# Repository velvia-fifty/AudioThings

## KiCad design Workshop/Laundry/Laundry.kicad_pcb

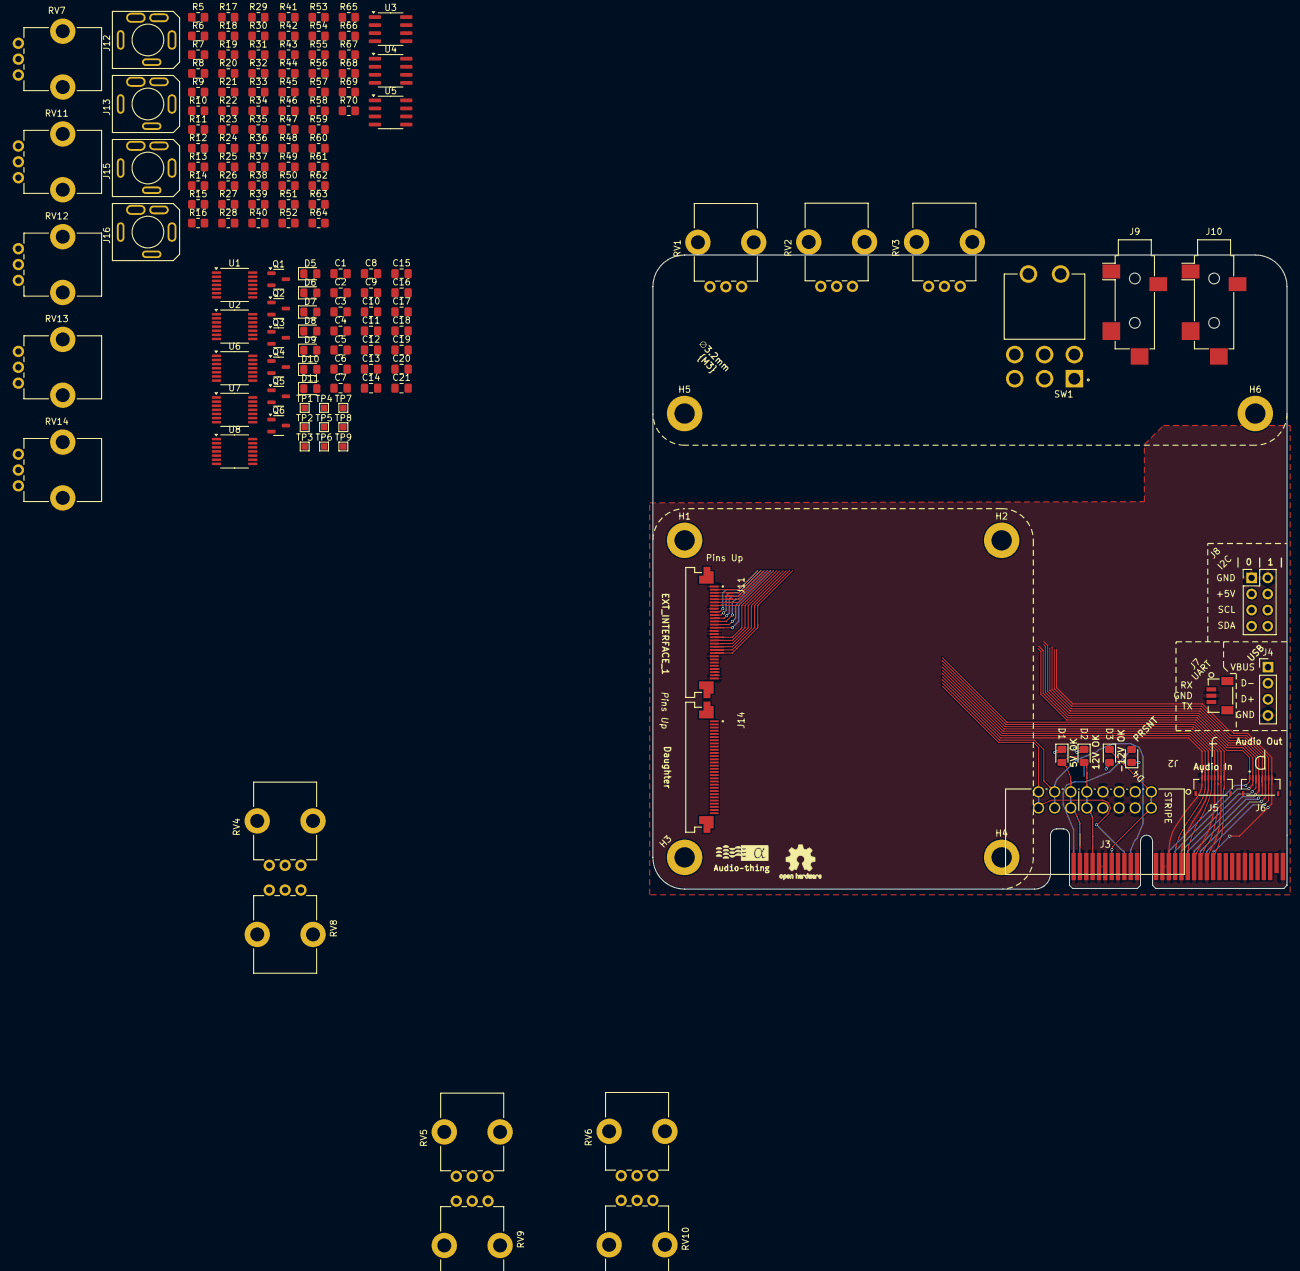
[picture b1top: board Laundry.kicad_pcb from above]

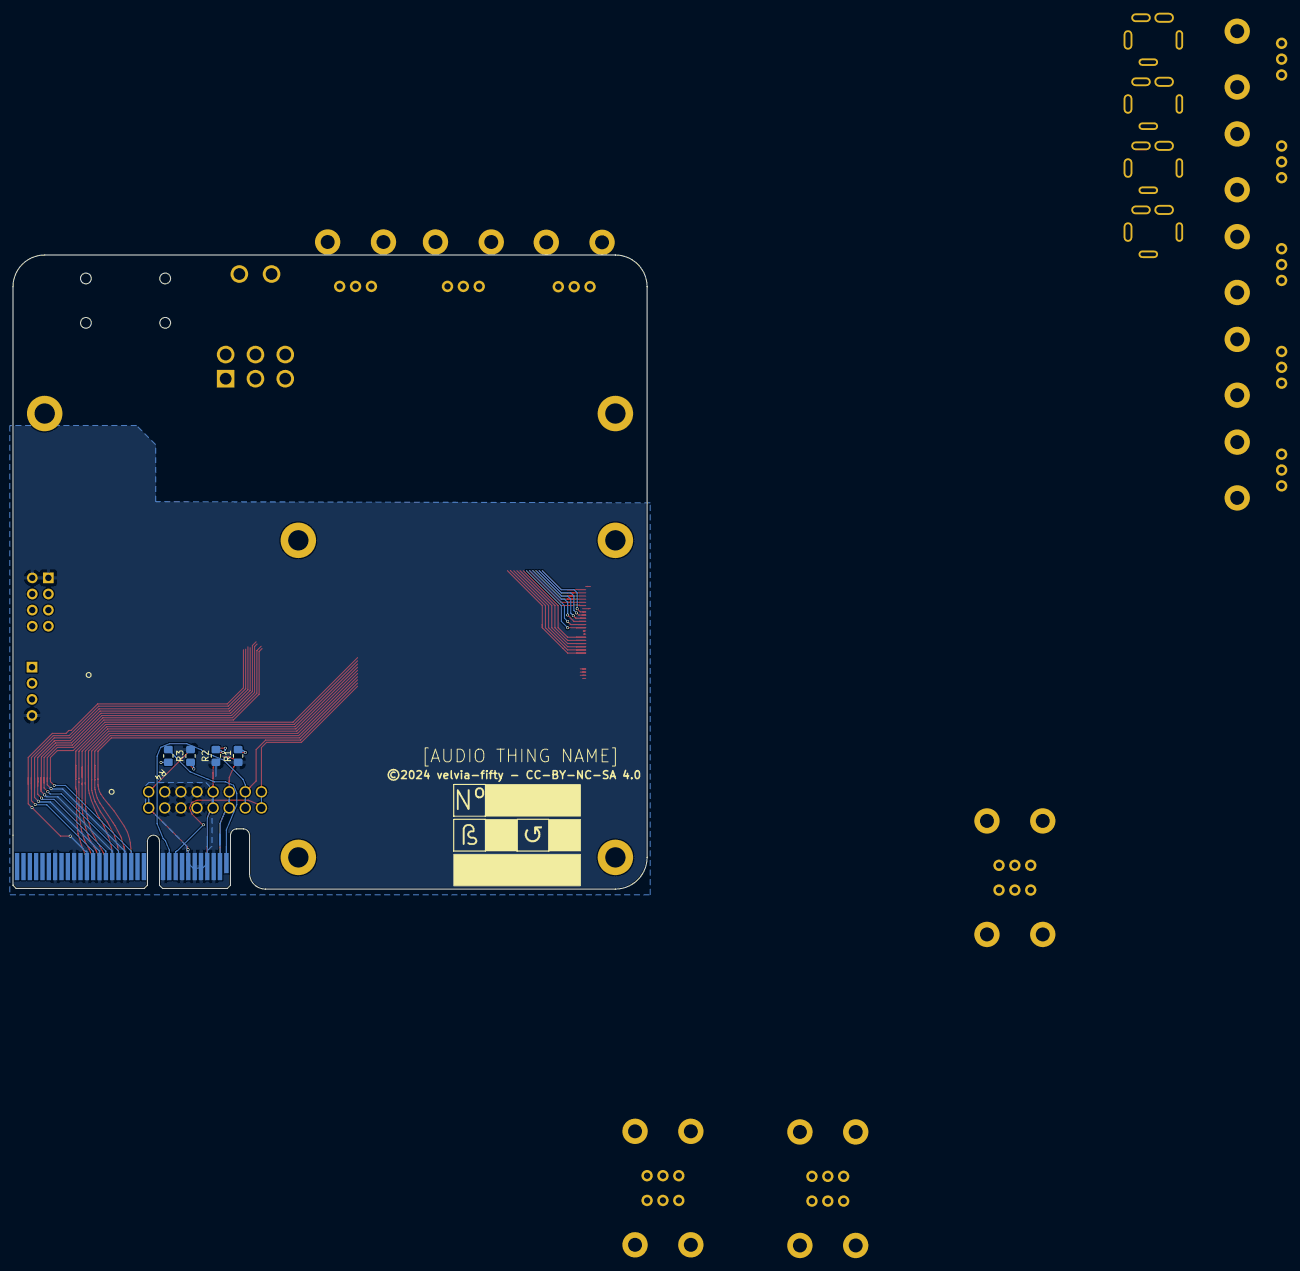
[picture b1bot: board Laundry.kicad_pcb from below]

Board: 2 copper layers, 100.0 x 100.0 mm, 161 parts (4 on the bottom side), 108 nets.

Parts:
C1: 10uf; C_0805_2012Metric_Pad1.18x1.45mm_HandSolder
C2: 1uf; C_0805_2012Metric_Pad1.18x1.45mm_HandSolder
C3: 100uf; C_0805_2012Metric_Pad1.18x1.45mm_HandSolder
C4, C5, C6: 100nf; C_0805_2012Metric_Pad1.18x1.45mm_HandSolder
C7, C8: 4.7nF; C_0805_2012Metric_Pad1.18x1.45mm_HandSolder
C9: 220nF; C_0805_2012Metric_Pad1.18x1.45mm_HandSolder
C10, C11: 100nF; C_0805_2012Metric_Pad1.18x1.45mm_HandSolder
C12: 10uF; C_0805_2012Metric_Pad1.18x1.45mm_HandSolder
C13: 68nF; C_0805_2012Metric_Pad1.18x1.45mm_HandSolder
C14, C21: 5.6nF; C_0805_2012Metric_Pad1.18x1.45mm_HandSolder
C15, C20: 2.2nF; C_0805_2012Metric_Pad1.18x1.45mm_HandSolder
C16, C18: 1uF; C_0805_2012Metric_Pad1.18x1.45mm_HandSolder
C17: 680p; C_0805_2012Metric_Pad1.18x1.45mm_HandSolder
C19: 680pF; C_0805_2012Metric_Pad1.18x1.45mm_HandSolder
D1: 5V OK; LED_0805_2012Metric_Pad1.15x1.40mm_HandSolder
D2: 12V OK; LED_0805_2012Metric_Pad1.15x1.40mm_HandSolder
D3: -12V OK; LED_0805_2012Metric_Pad1.15x1.40mm_HandSolder
D4: PRSNT; LED_0805_2012Metric_Pad1.15x1.40mm_HandSolder
D5, D6, D7: OSC; LED_0805_2012Metric_Pad1.15x1.40mm_HandSolder
D8, D9, D10: 1N4001; D_0805_2012Metric_Pad1.15x1.40mm_HandSolder
D11: LFO; LED_0805_2012Metric_Pad1.15x1.40mm_HandSolder
H1, H2, H3, H4, H5, H6: M3; MountingHole_3.2mm_M3_DIN965_Pad
J2: OPT EURO; EURORACK Right Angle
J3: BUS_PCIexpress_x4
J4: USB; PinHeader_1x04_P2.54mm_Vertical
J5: Audio In; AMPHENOL_F33B-1A7Q1-E8C08
J6: Audio Out; AMPHENOL_F33B-1A7Q1-E8C08
J7: UART; CONN_BM03B-SRSS-TBLFSN_JST
J8: I2C; PinHeader_2x04_P2.54mm_Vertical
J9, J10: Stereo Jack - SMD HZ; SMD_STEREO_CUI_SJ-3524-SMT_Horizontal
J11: EXT_INTERFACE_1; AMPHENOL_SFV30R-4STE1HLF - FFC - 30 RA
J12: TRI MIX OUT; SJ3-3505
J13: FOLD IN; SJ3-3505
J14: Daughter; AMPHENOL_SFV30R-4STE1HLF - FFC - 30 RA
J15: SYNC OUT; SJ3-3505
J16: SYNC IN; SJ3-3505
Q1, Q2: BC558; SOT-23-3
Q3, Q4, Q5, Q6: BC548; SOT-23-3
R1, R4: 150; R_0805_2012Metric_Pad1.20x1.40mm_HandSolder
R2, R3: 500; R_0805_2012Metric_Pad1.20x1.40mm_HandSolder
R5, R6, R7: 2k; R_0805_2012Metric_Pad1.20x1.40mm_HandSolder
R8, R9, R10, R14, R16, R18, R20, R22, R24, R38, R46, R48, R51, R59, R62: 1k; R_0805_2012Metric_Pad1.20x1.40mm_HandSolder
R11, R12, R13, R37, R40, R49, R52, R54, R58, R60, R61, R63, R64, R68: 100k; R_0805_2012Metric_Pad1.20x1.40mm_HandSolder
R15, R17, R19, R33, R35, R39, R41, R55: 10k; R_0805_2012Metric_Pad1.20x1.40mm_HandSolder
R21, R23, R25, R47: 1M; R_0805_2012Metric_Pad1.20x1.40mm_HandSolder
R26: 1.5k; R_0805_2012Metric_Pad1.20x1.40mm_HandSolder
R27, R43: 220k; R_0805_2012Metric_Pad1.20x1.40mm_HandSolder
R28: 100R; R_0805_2012Metric_Pad1.20x1.40mm_HandSolder
R29, R30, R31, R42, R44, R53: 20k; R_0805_2012Metric_Pad1.20x1.40mm_HandSolder
R32: 200k; R_0805_2012Metric_Pad1.20x1.40mm_HandSolder
R34: 51k; R_0805_2012Metric_Pad1.20x1.40mm_HandSolder
R36, R45, R57, R69: 680R; R_0805_2012Metric_Pad1.20x1.40mm_HandSolder
R50, R67: 470k; R_0805_2012Metric_Pad1.20x1.40mm_HandSolder
R56: 33k; R_0805_2012Metric_Pad1.20x1.40mm_HandSolder
R65: 4k7; R_0805_2012Metric_Pad1.20x1.40mm_HandSolder
R66: 47k; R_0805_2012Metric_Pad1.20x1.40mm_HandSolder
R70: 22k; R_0805_2012Metric_Pad1.20x1.40mm_HandSolder
RV1, RV2, RV3: PTV09 Pot HZ; Potentiometer_Bourns_PTV09A-1_Single_Vertical
RV4, RV5: 250k; Potentiometer_Bourns_PTV09A-1_Single_Vertical
RV6, RV8, RV9, RV10: 100k; Potentiometer_Bourns_PTV09A-1_Single_Vertical
RV7, RV11, RV13, RV14: 10k; Potentiometer_Bourns_PTV09A-1_Single_Vertical
RV12: 1M; Potentiometer_Bourns_PTV09A-1_Single_Vertical
SW1: Micro Toggle; DPDT Micro SW_1825138-7
TP1: SYNC1; TestPoint_Pad_1.0x1.0mm
TP2: SYNC2; TestPoint_Pad_1.0x1.0mm
TP3: SYNC3; TestPoint_Pad_1.0x1.0mm
TP4: SYNC4; TestPoint_Pad_1.0x1.0mm
TP5: TRI_A; TestPoint_Pad_1.0x1.0mm
TP6: WHT1; TestPoint_Pad_1.0x1.0mm
TP7: BLUE; TestPoint_Pad_1.0x1.0mm
TP8: WHT2; TestPoint_Pad_1.0x1.0mm
TP9: PINK; TestPoint_Pad_1.0x1.0mm
U1: 40106; TSSOP-14_4.4x5mm_P0.65mm
U2, U6, U7, U8: TL074; TSSOP-14_4.4x5mm_P0.65mm
U3, U4, U5: TL072; SOIC-8_3.9x4.9mm_P1.27mm

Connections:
+5V: D1.2 (A), J2.11, J2.12, J3.A2 (+5V), J3.B2 (+5V), J8.3, J8.4
+12V: D2.2 (A), J2.9, J2.10, J3.A4 (+12V), J3.B4 (+12V), R29.1, R30.1, R37.1, R49.1, R60.1
-12V: D3.1 (K), J2.1, J2.2, J3.A7 (-12V), J3.B7 (-12V), R42.2, R44.2
/Bus/CON_CV: J2.13, J2.14, J3.A10 (EURO_CV)
/Bus/CON_GATE: J2.15, J2.16, J3.A9 (EURO_GATE)
/Bus/I2C0_SCL: J3.B23 (I2C0_SCL), J8.5
/Bus/I2C0_SDA: J3.A24 (I2C0_SDA), J8.7
/Bus/I2C1_SCL: J3.A27 (I2C1_SCL), J8.6
/Bus/I2C1_SDA: J3.B27 (I2C1_SDA), J8.8
/Bus/USB_D+: J3.B12 (USB_D+), J4.3
/OSC/BLUE: R51.2, TP7.1
/OSC/FMV_IN: C7.1, R26.1
/OSC/FOLD_0_IN: J13.T, R34.2, TP5.1
/OSC/PINK: R62.2, TP9.1
/OSC/SQ_LOW_0: C4.2, R21.1
/OSC/SQ_MID_0: C5.2, R23.1
/OSC/SQ_TRB_0: C6.2, R25.1
/OSC/SYNC_IN_0: D8.2 (A), J16.T, TP1.1
/OSC/TRI_LOW_0: R14.2, R20.1, RV8.3
/OSC/TRI_MID_0: R16.2, R22.1, RV9.3
/OSC/TRI_TRB_0: R18.2, R24.1, RV10.3
/OSC/WHT_1: R48.1, TP6.1
/OSC/WHT_2: R59.1, TP8.1
GND: C1.1, C2.1, C3.1, C12.2, C13.1, D11.1 (K), J2.3, J2.4, J2.5, J2.6, J2.7, J2.8, J3.A3 (GND), J3.A5 (GND), J3.A6 (GND), J3.A8 (GND), J3.A11 (GND), J3.A15 (GND), J3.A17 (GND), J3.A19 (GND), J3.A21 (GND), J3.A23 (GND), J3.A26 (GND), J3.B1 (GND), J3.B3 (GND), J3.B5 (GND), J3.B6 (GND), J3.B8 (GND), J3.B11 (GND), J3.B13 (GND), J3.B14 (GND), J3.B16 (GND), J3.B18 (GND), J3.B20 (GND), J3.B26 (GND), J3.B32 (GND), J4.4, J5.1, J5.3, J5.5, J5.7, J6.2, J6.4, J6.6, J6.8, J7.2, J8.1, J8.2, J11.1, J11.8, J11.15, J11.16, J11.23, J11.30, J12.S, J13.S, J15.S, J16.S, Q5.2 (B), Q6.2 (B), R1.1, R2.1, R3.2, R5.1, R6.1, R7.1, R15.2, R17.2, R19.2, R20.2, R21.2, R22.2, R23.2, R24.2, R25.2, R40.2, R45.2, R46.2, R52.2, R53.2, R57.2, R58.2, R63.2, R65.2, R66.2, R67.2, R69.2, R70.2, RV8.1, RV9.1, RV10.1, RV11.3, RV14.3, U4.3 (+), U5.3 (+)
unnamed: C1.2, R8.1, R14.1, RV4.2, RV4.3, U1.3
unnamed: C2.2, R9.1, R16.1, RV5.2, RV5.3, U1.5
unnamed: C3.2, R10.1, R18.1, RV6.2, RV6.3, U1.11
unnamed: C7.2, C8.2, RV7.1
unnamed: C8.1, R28.1
unnamed: C9.2, RV11.2
unnamed: C10.2, R39.1, R43.2, U6.1
unnamed: C11.1, R45.1, RV14.2
unnamed: C9.1, C11.2, R26.2, R36.1
unnamed: C13.2, R36.2, RV7.3, RV14.1
unnamed: C14.1, C15.1, C17.1, R48.2, R54.2, U8.1
unnamed: C14.2, R47.1
unnamed: C15.2, R50.1
unnamed: C17.2, R55.1
unnamed: C19.1, R65.1
unnamed: C20.1, R66.1
unnamed: C21.1, R67.1
unnamed: D1.1 (K), R1.2
unnamed: D2.1 (K), R2.2
unnamed: D3.2 (A), R3.1
unnamed: D4.2 (A), J3.B31 (PRSNT_B)
unnamed: D4.1 (K), R4.2
unnamed: D5.2 (A), D9.2 (A), R11.1, RV4.1, TP2.1, U1.4
unnamed: D5.1 (K), R5.2
unnamed: D6.1 (K), R6.2
unnamed: D7.2 (A), R13.1, RV6.1, TP4.1, U1.10
unnamed: D7.1 (K), R7.2
unnamed: D8.1 (K), R8.2
unnamed: D9.1 (K), R9.2
unnamed: D6.2 (A), D10.2 (A), R12.1, RV5.1, TP3.1, U1.6
unnamed: D10.1 (K), R10.2
unnamed: D11.2 (A), R41.1
unnamed: J3.B15 (Audio_In_A), J5.2
unnamed: J3.B17 (Audio_In_B), J5.4
unnamed: J3.B19 (Audio_In_C), J5.6
unnamed: J3.B21 (Audio_In_D), J5.8
unnamed: J3.A14 (Audio_Out_A), J6.1
unnamed: J3.A16 (Audio_Out_B), J6.3
unnamed: J3.A18 (Audio_Out_C), J6.5
unnamed: J3.A20 (Audio_Out_D), J6.7
unnamed: J3.A1 (PRSNT_A), R4.1
unnamed: J3.B22 (UART_RX), J7.1
unnamed: J3.A22 (UART_TX), J7.3
unnamed: J3.A12 (USB_5V), J4.1
unnamed: J3.A13 (USB_D-), J4.2
unnamed: J12.T, J13.TN, RV8.2, RV9.2, RV10.2
unnamed: Q1.2 (B), Q3.2 (B), U3.1, U3.2 (-)
unnamed: Q1.1 (C), Q3.1 (C), R33.2
unnamed: Q1.3 (E), R29.2
unnamed: Q2.2 (B), Q4.2 (B), R31.2, U4.1
unnamed: Q2.1 (C), Q4.1 (C), R35.2
unnamed: Q2.3 (E), R30.2
unnamed: Q3.3 (E), R42.1
unnamed: Q4.3 (E), R44.1
unnamed: C16.1, Q5.3 (E), R49.2
unnamed: C18.1, Q6.3 (E), R60.2
unnamed: R28.2, RV11.1
unnamed: R32.2, R38.2, U5.1
unnamed: R39.2, RV12.2, RV12.3
unnamed: R46.1, RV13.2, RV13.3
unnamed: R51.1, R56.2, U8.8
unnamed: R59.2, R61.1, R64.2, U8.7
unnamed: R62.1, R68.2, U8.14
unnamed: R11.2, R15.1, U2.3 (+)
unnamed: C4.1, U2.1, U2.2 (-)
unnamed: R12.2, R17.1, U2.5 (+)
unnamed: C5.1, U2.6 (-), U2.7
unnamed: R13.2, R19.1, U2.12 (+)
unnamed: C6.1, U2.13 (-), U2.14
unnamed: R34.1, RV13.1, U3.3 (+)
unnamed: R31.1, R33.1, U4.2 (-)
unnamed: R32.1, R35.1, U5.2 (-)
unnamed: C10.1, R27.1, U6.3 (+)
unnamed: R37.2, R40.1, R43.1, U6.2 (-)
unnamed: C12.1, R27.2, RV12.1, U7.3 (+)
unnamed: J15.T, J16.TN, R41.2, U7.1, U7.2 (-)
unnamed: C16.2, R52.1, U8.3 (+)
unnamed: R54.1, R57.1, U8.2 (-)
unnamed: C18.2, R63.1, U8.5 (+)
unnamed: R64.1, R69.1, U8.6 (-)
unnamed: R47.2, R50.2, R53.1, R55.2, U8.10 (+)
unnamed: R56.1, R58.1, U8.9 (-)
unnamed: C19.2, C20.2, C21.2, R61.2, U8.12 (+)
unnamed: R68.1, R70.1, U8.13 (-)

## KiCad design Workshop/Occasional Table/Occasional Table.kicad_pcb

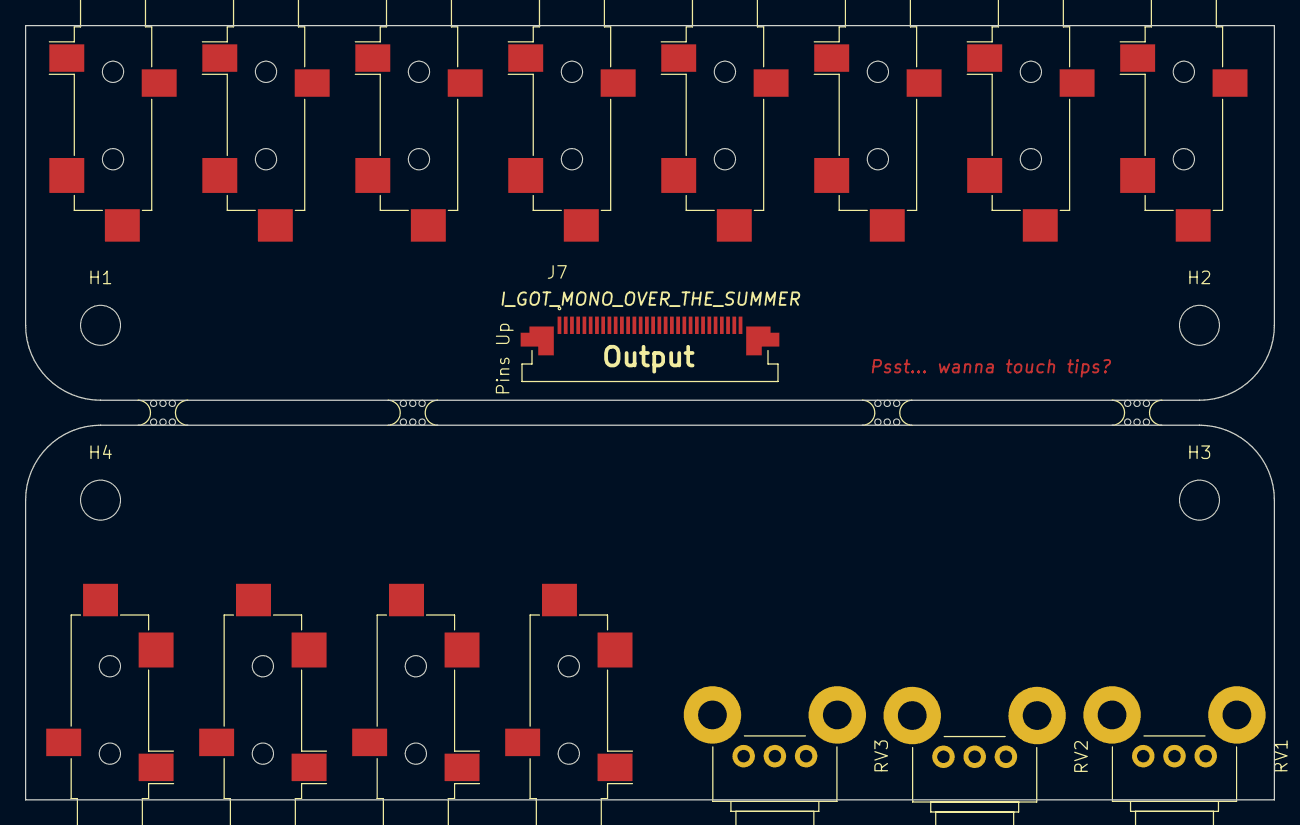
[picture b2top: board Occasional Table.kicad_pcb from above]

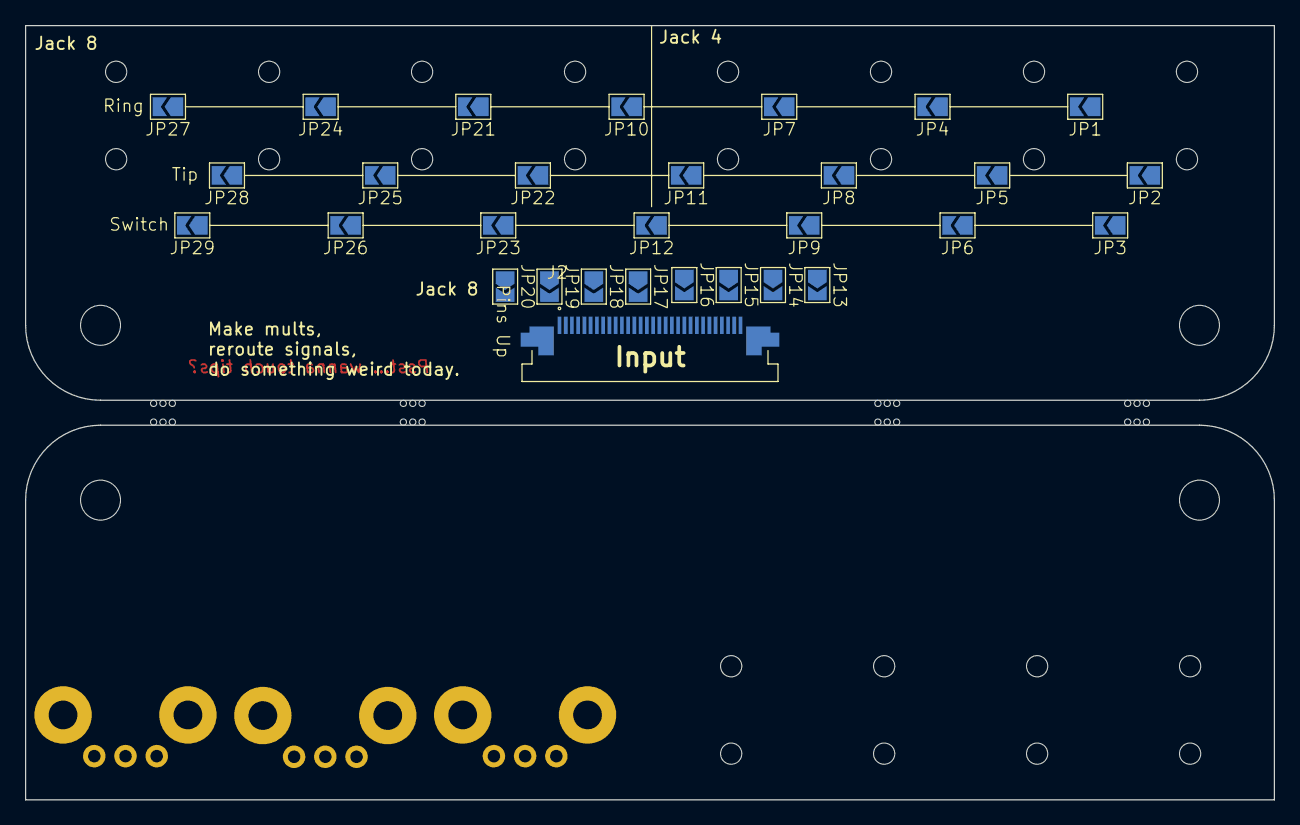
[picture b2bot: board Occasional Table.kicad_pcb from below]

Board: 2 copper layers, 100.0 x 62.0 mm, 54 parts (30 on the bottom side), 33 nets, no tracks yet.

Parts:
H1, H2, H3, H4: Spacer M3; MountingHole_3.2mm_M3_DIN965
J1: Jack 1; Jack_3.5mm_CUI_SJ-3524-SMT_Horizontal
J2: EXT_INTERFACE_1; AMPHENOL_SFV30R-4STE1HLF - FFC - 30 RA
J4: Jack 2; Jack_3.5mm_CUI_SJ-3524-SMT_Horizontal
J5: Jack 3; Jack_3.5mm_CUI_SJ-3524-SMT_Horizontal
J6: Jack 4; Jack_3.5mm_CUI_SJ-3524-SMT_Horizontal
J7: I_GOT_MONO_OVER_THE_SUMMER; AMPHENOL_SFV30R-4STE1HLF - FFC - 30 RA
J8, J13: Jack 5; Jack_3.5mm_CUI_SJ-3524-SMT_Horizontal
J9, J14: Jack 6; Jack_3.5mm_CUI_SJ-3524-SMT_Horizontal
J10, J16: Jack 7; Jack_3.5mm_CUI_SJ-3524-SMT_Horizontal
J11, J17: Jack 8; Jack_3.5mm_CUI_SJ-3524-SMT_Horizontal
JP1, JP2, JP3, JP4, JP5, JP6, JP7, JP8, JP9, JP10, JP11, JP12, JP21, JP22, JP23, JP24, JP25, JP26, JP27, JP28, JP29: Mult Down; SolderJumper-2_P1.3mm_Open_TrianglePad1.0x1.5mm
JP13: Touch Tips 1; SolderJumper-2_P1.3mm_Open_TrianglePad1.0x1.5mm
JP14: Touch Tips 2; SolderJumper-2_P1.3mm_Open_TrianglePad1.0x1.5mm
JP15: Touch Tips 3; SolderJumper-2_P1.3mm_Open_TrianglePad1.0x1.5mm
JP16: Touch Tips 4; SolderJumper-2_P1.3mm_Open_TrianglePad1.0x1.5mm
JP17: Touch Tips 5; SolderJumper-2_P1.3mm_Open_TrianglePad1.0x1.5mm
JP18: Touch Tips 6; SolderJumper-2_P1.3mm_Open_TrianglePad1.0x1.5mm
JP19: Touch Tips 7; SolderJumper-2_P1.3mm_Open_TrianglePad1.0x1.5mm
JP20: Touch Tips 8; SolderJumper-2_P1.3mm_Open_TrianglePad1.0x1.5mm
RV1: POT A; Potentiometer_Bourns_PTV09A-2_Single_Horizontal
RV2: POT B; Potentiometer_Bourns_PTV09A-2_Single_Horizontal
RV3: POT C; Potentiometer_Bourns_PTV09A-2_Single_Horizontal
mouse-bite-2mm-slot, mouse-bite-2mm-slot#2, mouse-bite-2mm-slot#3, mouse-bite-2mm-slot#4: VAL**; mouse-bite-2mm-slot

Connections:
/Octo-jack/EXT_JACK_R_1: J1.R, J2.4, JP1.1 (A)
/Octo-jack/EXT_JACK_R_2: J2.7, J4.R, JP1.2 (B), JP4.1 (A)
/Octo-jack/EXT_JACK_R_3: J2.11, J5.R, JP4.2 (B), JP7.1 (A)
/Octo-jack/EXT_JACK_R_4: J2.14, J6.R, JP7.2 (B), JP10.1 (A)
/Octo-jack/EXT_JACK_R_5: J2.19, J8.R, JP10.2 (B), JP21.1 (A)
/Octo-jack/EXT_JACK_R_6: J2.22, J9.R, JP21.2 (B), JP24.1 (A)
/Octo-jack/EXT_JACK_R_7: J2.26, J10.R, JP24.2 (B), JP27.1 (A)
/Octo-jack/EXT_JACK_R_8: J2.29, J11.R, JP27.2 (B)
/Octo-jack/EXT_JACK_TN_1: J1.TN, J2.3, JP3.1 (A)
/Octo-jack/EXT_JACK_TN_2: J2.6, J4.TN, JP3.2 (B), JP6.1 (A)
/Octo-jack/EXT_JACK_TN_3: J2.10, J5.TN, JP6.2 (B), JP9.1 (A)
/Octo-jack/EXT_JACK_TN_4: J2.13, J6.TN, JP9.2 (B), JP12.1 (A)
/Octo-jack/EXT_JACK_TN_5: J2.18, J8.TN, JP12.2 (B), JP23.1 (A)
/Octo-jack/EXT_JACK_TN_6: J2.21, J9.TN, JP23.2 (B), JP26.1 (A)
/Octo-jack/EXT_JACK_TN_7: J2.25, J10.TN, JP26.2 (B), JP29.1 (A)
/Octo-jack/EXT_JACK_TN_8: J2.28, J11.TN, JP29.2 (B)
/Octo-jack/EXT_JACK_T_1: J1.T, J2.2, JP2.1 (A), JP13.1 (A)
/Octo-jack/EXT_JACK_T_2: J2.5, J4.T, JP2.2 (B), JP5.1 (A), JP14.1 (A)
/Octo-jack/EXT_JACK_T_3: J2.9, J5.T, JP5.2 (B), JP8.1 (A), JP15.1 (A)
/Octo-jack/EXT_JACK_T_4: J2.12, J6.T, JP8.2 (B), JP11.1 (A), JP16.1 (A)
/Octo-jack/EXT_JACK_T_5: J2.17, J8.T, JP11.2 (B), JP17.1 (A), JP22.1 (A)
/Octo-jack/EXT_JACK_T_6: J2.20, J9.T, JP18.1 (A), JP22.2 (B), JP25.1 (A)
/Octo-jack/EXT_JACK_T_7: J2.24, J10.T, JP19.1 (A), JP25.2 (B), JP28.1 (A)
/Octo-jack/EXT_JACK_T_8: J2.27, J11.T, JP20.1 (A), JP28.2 (B)
/Octo-jack/RELAY_JACK_T_1: J7.2, J7.3, J7.4, JP13.2 (B)
/Octo-jack/RELAY_JACK_T_2: J7.5, J7.6, J7.7, JP14.2 (B)
/Octo-jack/RELAY_JACK_T_3: J7.9, J7.10, J7.11, JP15.2 (B)
/Octo-jack/RELAY_JACK_T_4: J7.12, J7.13, J7.14, JP16.2 (B)
/Octo-jack/RELAY_JACK_T_5: J7.17, J7.18, J7.19, JP17.2 (B)
/Octo-jack/RELAY_JACK_T_6: J7.20, J7.21, J7.22, JP18.2 (B)
/Octo-jack/RELAY_JACK_T_7: J7.24, J7.25, J7.26, JP19.2 (B)
/Octo-jack/RELAY_JACK_T_8: J7.27, J7.28, J7.29, JP20.2 (B)
GND: J1.S, J2.1, J2.8, J2.15, J2.16, J2.23, J2.30, J4.S, J5.S, J6.S, J7.1, J7.8, J7.15, J7.16, J7.23, J7.30, J8.S, J9.S, J10.S, J11.S, J13.S, J14.S, J16.S, J17.S

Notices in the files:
Workshop/Laundry/Laundry.kicad_pcb:
©2024 velvia-fifty - CC-BY-NC-SA 4.0
